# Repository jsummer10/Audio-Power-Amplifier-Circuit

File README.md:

# Power Amplifier Circuit Design 

## Simulation

Simulation was performed using OrCAD's PSpice software. 

## Eagle

PCB design schematic created using Autodesk's Eagle software 

Adafruit extension was used to create certain packages. Adafruit install instructions can be found [here](https://www.autodesk.com/products/eagle/blog/library-basics-install-use-sparkfun-adafruit-libraries-autodesk-eagle/)

## PCB Design

### PCB Top

### PCB Bottom

## Completed Amplifier

## Author

- Jake Summerville

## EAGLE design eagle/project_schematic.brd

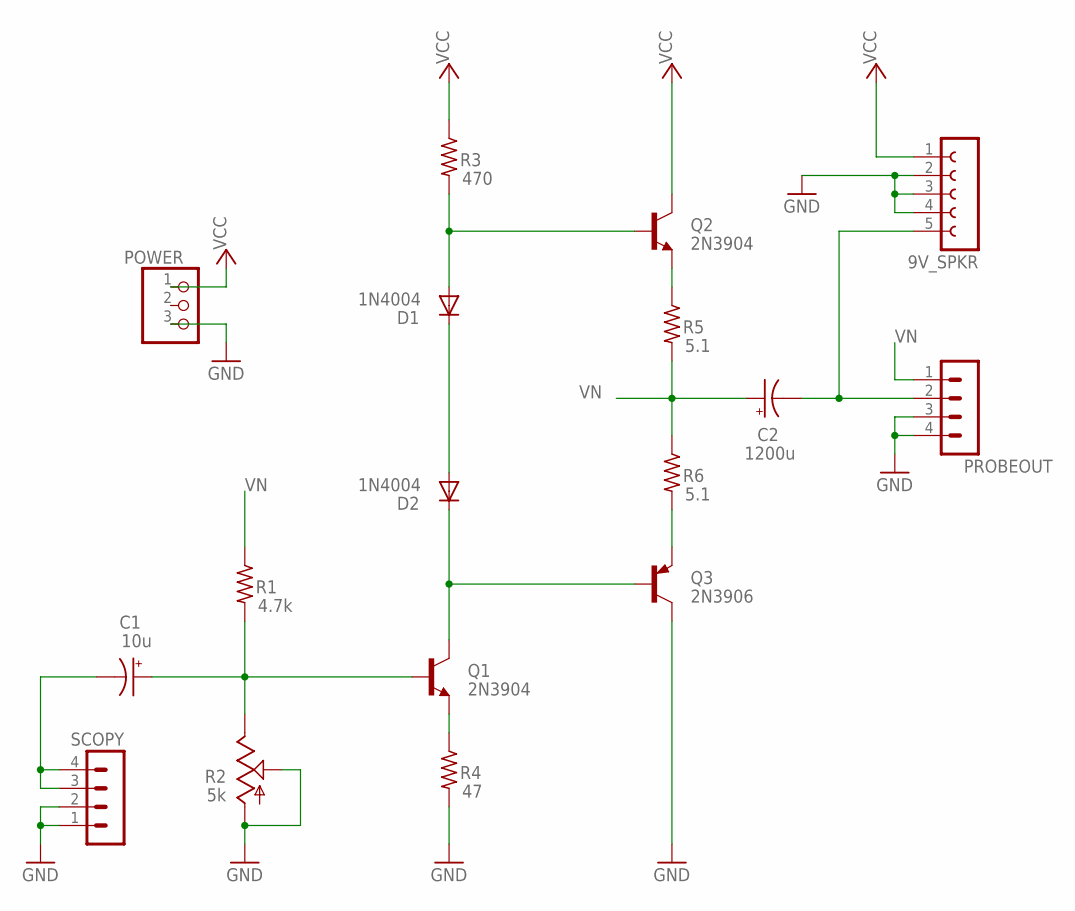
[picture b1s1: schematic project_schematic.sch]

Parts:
9V_SPKR: FE05-1
C1: 10u; E5-8,5
C2: 1200u; E5-10,5
D1, D2: 1N4004; DO41-10
POWER: PINHD-1X3; 1X03
PROBEOUT: MA04-1
Q1, Q2: 2N3904; TO92
Q3: 2N3906; TO92
R1: 4.7k; 0204/7
R2: 5k; CA6V
R3: 470; 0204/7
R4: 47; 0204/7
R5, R6: 5.1; 0204/7
SCOPY: MA04-1

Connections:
GND: 9V_SPKR.2, 9V_SPKR.3, 9V_SPKR.4, POWER.3, PROBEOUT.3, PROBEOUT.4, SCOPY.1, SCOPY.2
unnamed: C1.+, Q1.2 (B), R1.2, R2.E
unnamed: Q1.3 (E), R4.1
unnamed: D2.C, Q1.1 (C), Q3.2 (B)
unnamed: D1.A, Q2.2 (B), R3.2
unnamed: D1.C, D2.A
unnamed: Q2.3 (E), R5.1
unnamed: Q3.3 (E), R6.2
unnamed: 9V_SPKR.5, C2.-, PROBEOUT.2
unnamed: R2.A, R2.S
unnamed: C1.-, SCOPY.3, SCOPY.4
VCC: POWER.1, R3.1
VN: C2.+, PROBEOUT.1, R1.1, R5.2, R6.1

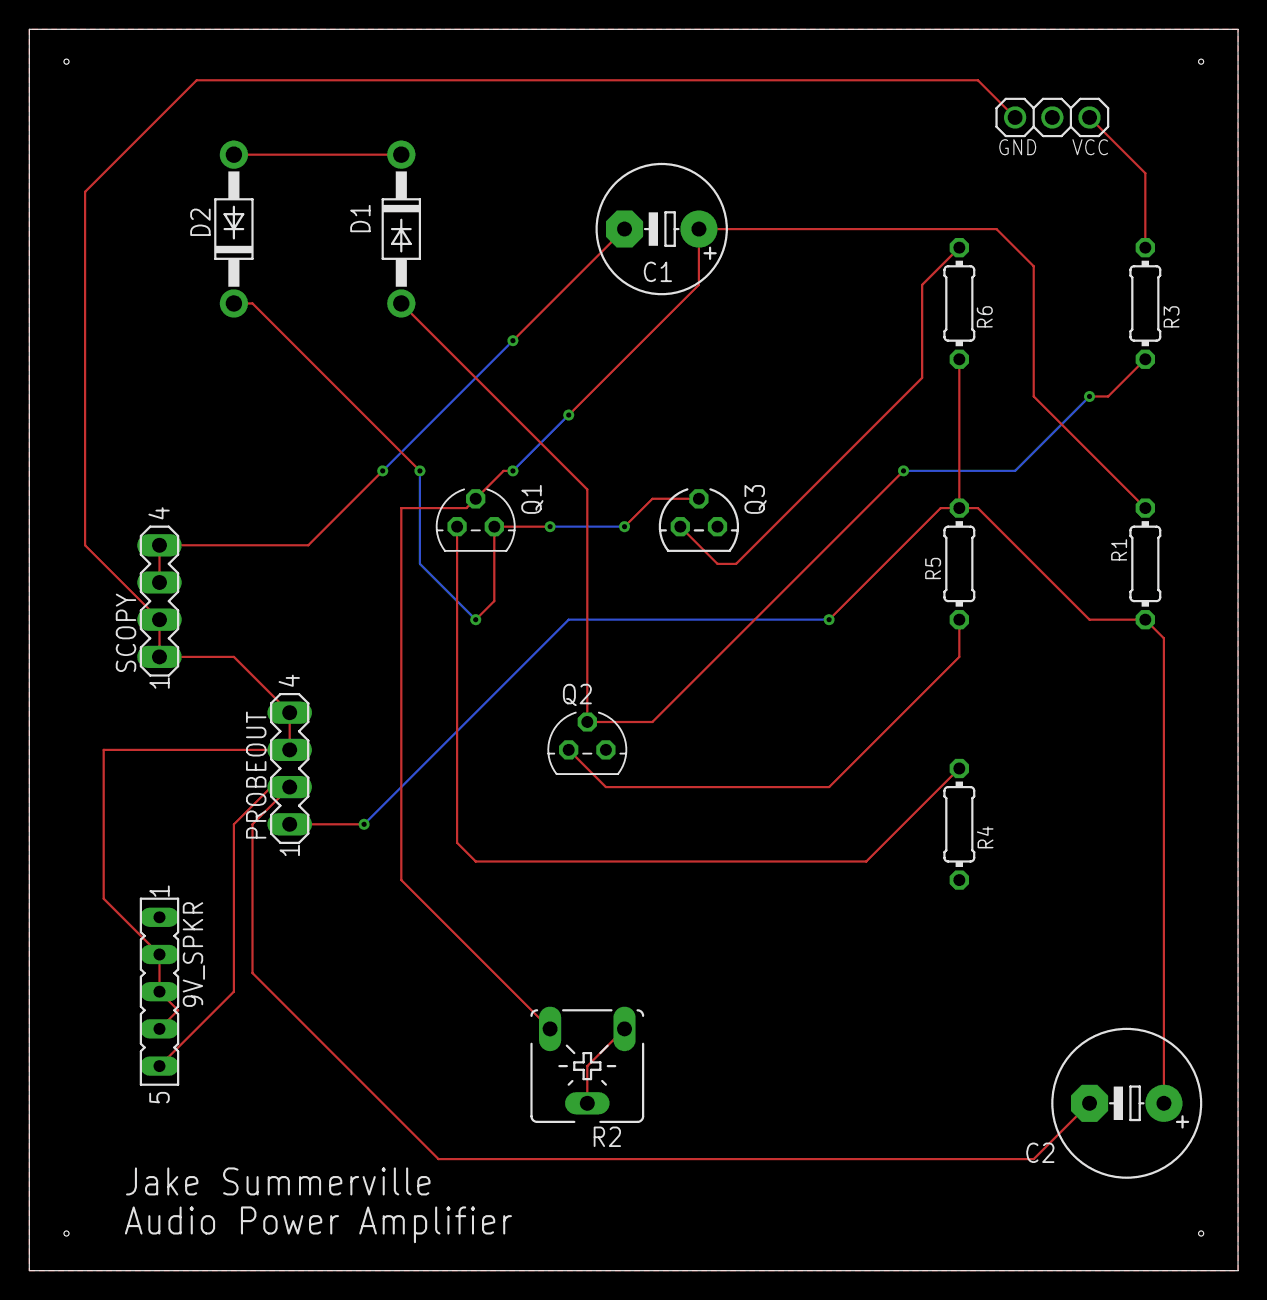
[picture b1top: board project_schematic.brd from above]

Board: 2 copper layers, 82.5 x 84.8 mm, 17 parts (0 on the bottom side), 13 nets.

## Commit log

2021-04-16 pspice design
2021-04-16 eagle design
2021-04-16 PCB Design
2021-04-16 Update design
2021-04-16 Update schematics
2021-04-16 Rename dir
2021-04-16 Increased size
2021-04-29 Resolve issues
2021-08-17 Add finished product
